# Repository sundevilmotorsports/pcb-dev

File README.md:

# Sun Devil Motorsports Data Acquisition PCB Repository
## About
Various PCB projects for Data Acquisition. Includes:
- SDM-22 Main Board
- SDM-22 Wheel Board
- SDM CAN Board (Texas Instruments SN65HVD230)
- SDM KiCad library (submodule)
- SDM-23 things
- SDM-24 things
## Installation Requirements
- KiCad 6
- `SDM.pretty`, `SDM_kicad`, `teensy.pretty`, `teensy_library` (included here as submodules)
## Installation Instructions
1. Get the project.
```bash
$ git clone --recursive git@github.com:sundevilmotorsports/pcb-dev.git
```
2. Add `SDM.pretty`, `SDM_kicad`, `teensy.pretty`, `teensy_library` as libraries in KiCad.

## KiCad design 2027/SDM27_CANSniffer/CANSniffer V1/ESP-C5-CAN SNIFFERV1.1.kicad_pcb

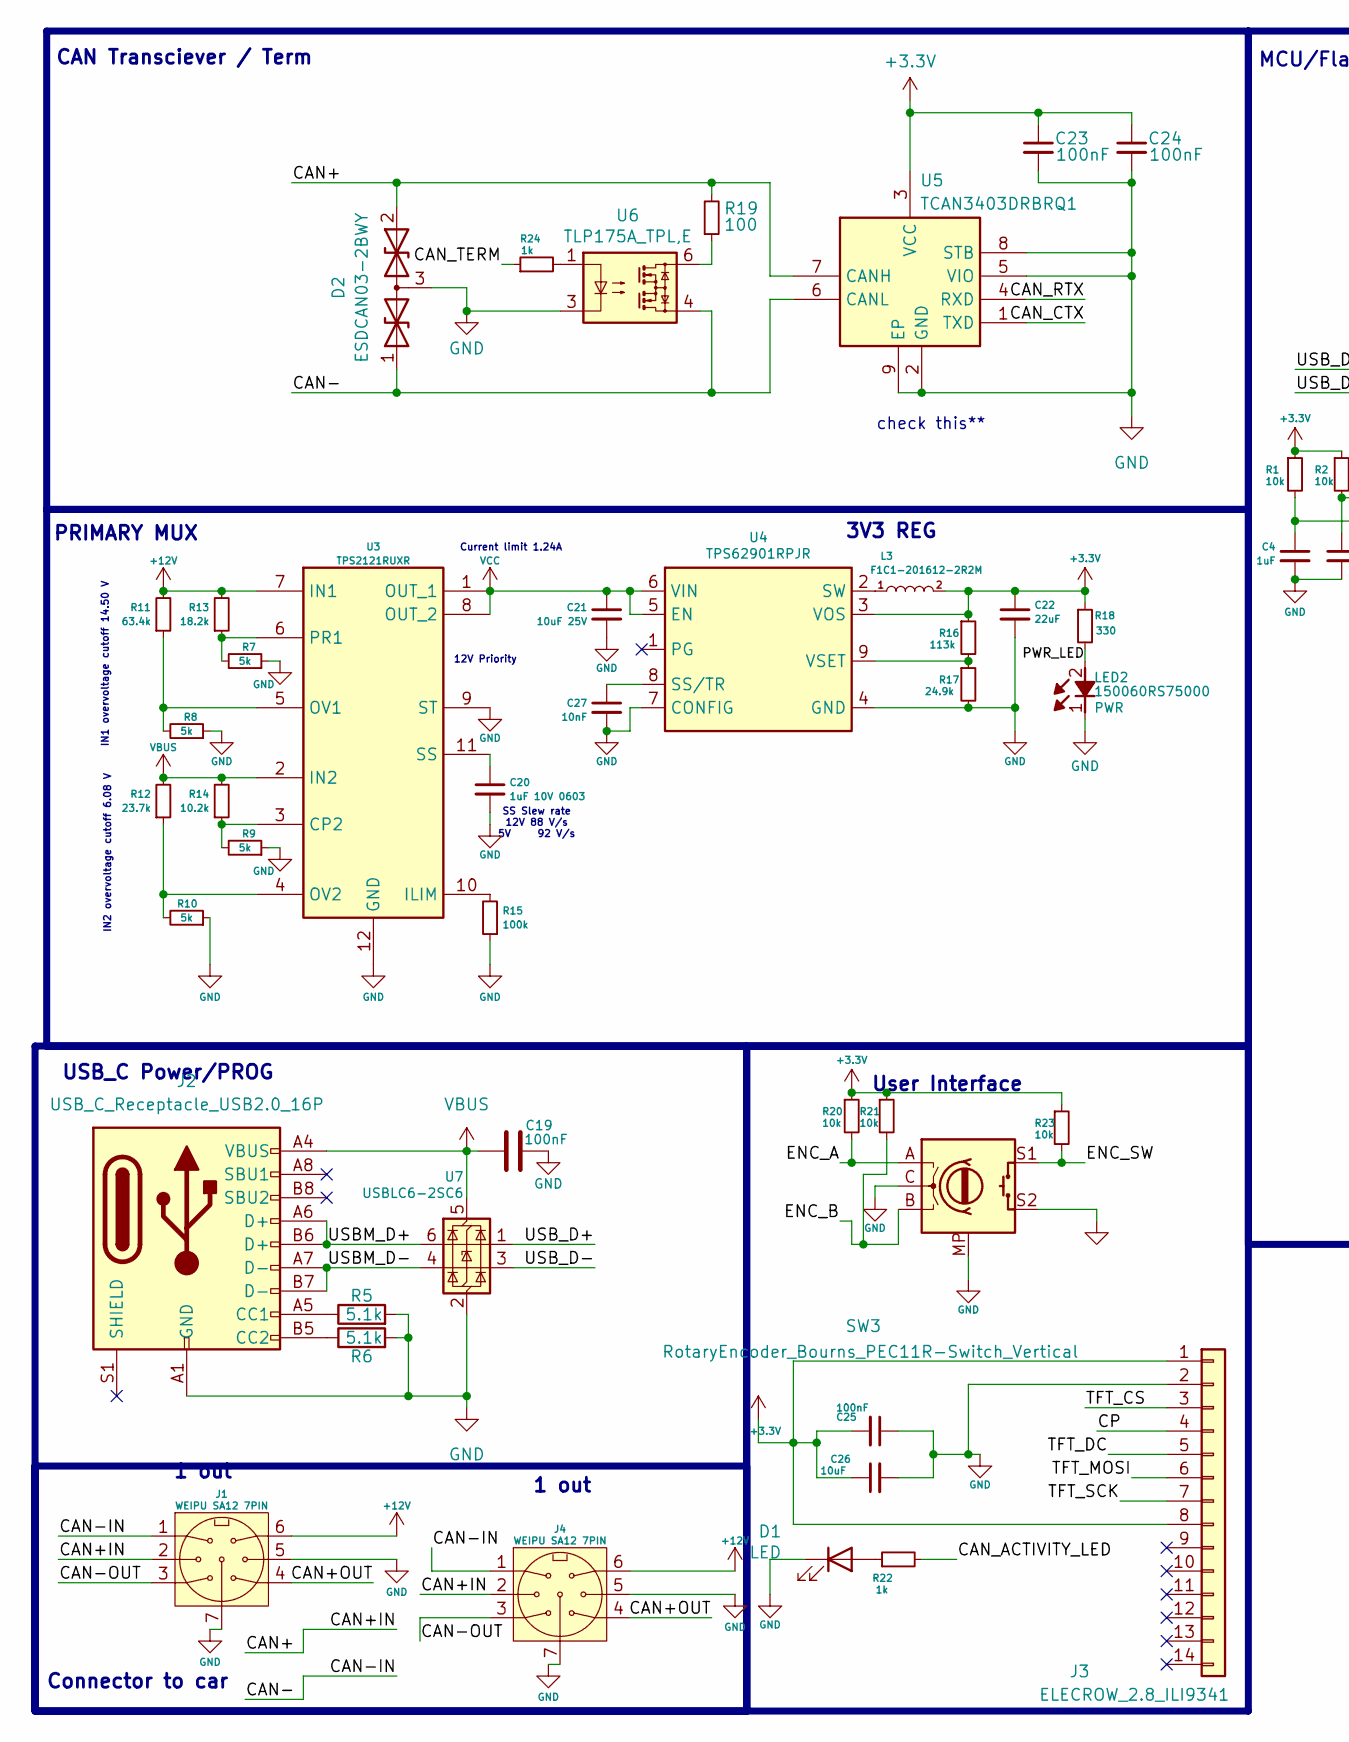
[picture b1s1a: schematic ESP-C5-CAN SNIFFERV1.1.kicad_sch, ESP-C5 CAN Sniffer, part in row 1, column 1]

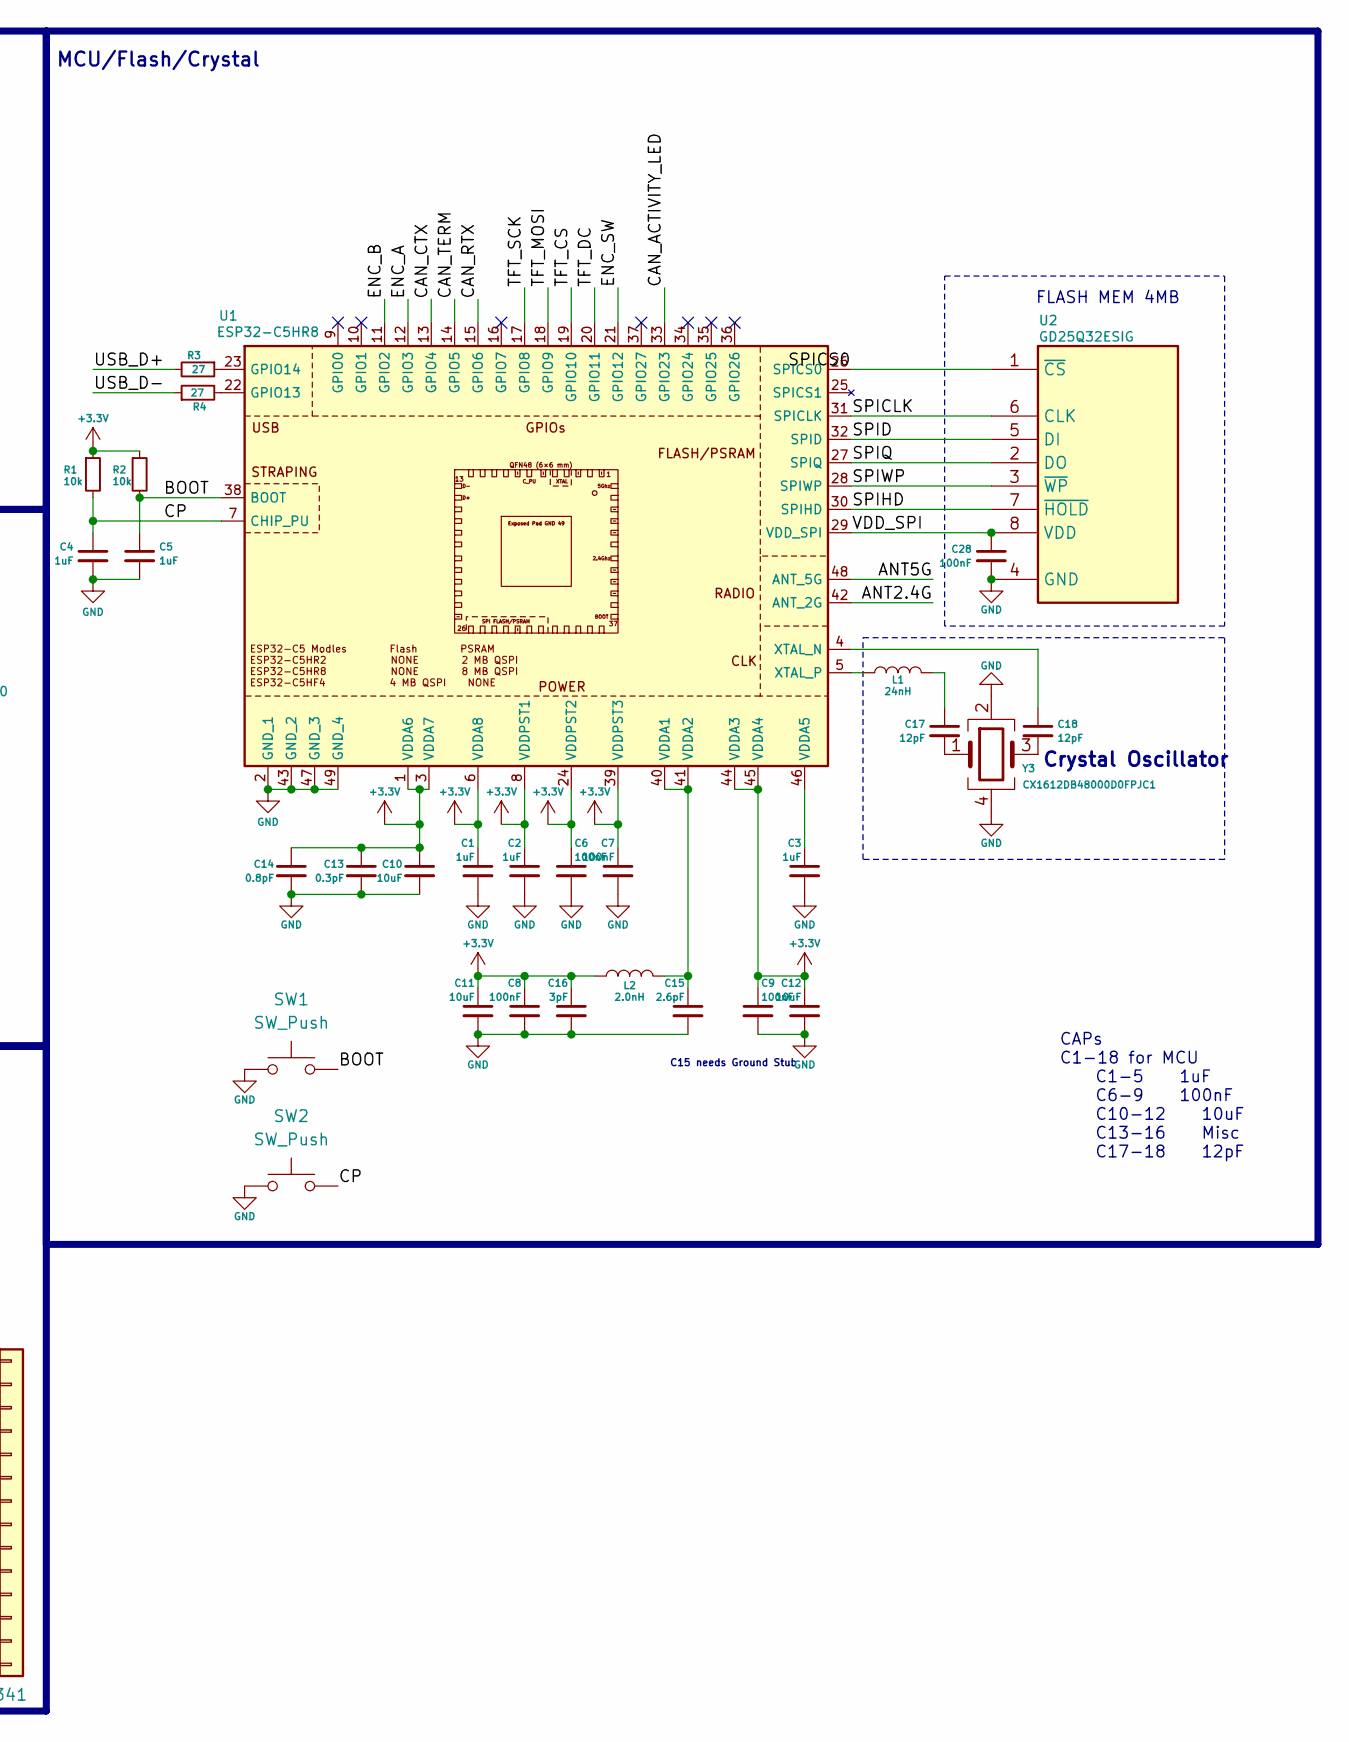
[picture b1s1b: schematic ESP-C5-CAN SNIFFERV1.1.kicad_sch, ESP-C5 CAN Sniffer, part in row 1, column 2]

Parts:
C1, C2, C3, C4, C5: 1uF; C_0603_1608Metric
C6, C7, C8, C9, C19, C23, C24, C25, C28: 100nF; C_0603_1608Metric
C10, C11, C12, C26: 10uF; C_0603_1608Metric
C13: 0.3pF; C_0603_1608Metric
C14: 0.8pF; C_0603_1608Metric
C15: 2.6pF; C_0603_1608Metric
C16: 3pF; C_0603_1608Metric
C17, C18: 12pF; C_0201_0603Metric
C20: 1uF 10V 0603; C_0603_1608Metric
C21: 10uF 25V; C_0603_1608Metric
C22: 22uF; C_0603_1608Metric
C27: 10nF; C_0603_1608Metric
D1: LED; SSFLXH100LID01
D2: ESDCAN03-2BWY; SOT65P210X110-3N; Mouser Part Number 511-ESDCAN03-2BWY
J1, J4: WEIPU SA12 7PIN; PinHeader_1x07_P2.54mm_Vertical
J2: USB_C_Receptacle_USB2.0_16P; USB_C_Receptacle_G-Switch_GT-USB-7010ASVCAN
J3: ELECROW_2.8_ILI9341; PinHeader_1x14_P2.54mm_Vertical
L1: 24nH; L_0402_1005Metric
L2: 2.0nH; L_0402_1005Metric
L3: F1C1-201612-2R2M; F1C12016122R2M; Mouser Part Number 530-F1C1-201612-2R2M
LED2: 150060RS75000; LEDC1608X80N; Mouser Part Number 710-150060RS75000
R1, R2, R20, R21, R23: 10k; R_0402_1005Metric
R3, R4: 27; R_0402_1005Metric
R5, R6: 5.1k; R_0603_1608Metric
R7, R8, R9, R10: 5k; R_0603_1608Metric
R11: 63.4k; R_0603_1608Metric
R12: 23.7k; R_0603_1608Metric
R13: 18.2k; R_0603_1608Metric
R14: 10.2k; R_0603_1608Metric
R15: 100k; R_0603_1608Metric
R16: 113k; R_0603_1608Metric
R17: 24.9k; R_0603_1608Metric
R18: 330; R_0603_1608Metric
R19: 100; R_0603_1608Metric
R22, R24: 1k; R_0402_1005Metric
SW1, SW2: SW_Push; SW_SPST_CK_KXT3
SW3: RotaryEncoder_Bourns_PEC11R-Switch_Vertical; XDCR_PEC11R-4220F-S0024
U1: ESP32-C5HR8; QFN40P600X600X90-49N-D; Manufacturer_Part_Number ESP32-C5HR8
U2: GD25Q32ESIG; SOP-8-1EP_4.57x4.57mm_P1.27mm_EP4.57x4.45mm; Mouser Part Number 363-GD25Q32ESIG
U3: TPS2121RUXR; Mouser Part Number 595-TPS2121RUXR
U4: TPS62901RPJR; Mouser Part Number 595-TPS62901RPJR
U5: TCAN3403DRBRQ1; SON65P300X300X100-9N-D; Manufacturer_Part_Number TCAN3403DRBRQ1; Mouser Part Number 595-TCAN3403DRBRQ1
U6: TLP175A_TPL,E; TLP266J; Mouser Part Number 757-TLP175A(TPLE
U7: USBLC6-2SC6; SOT-23-6
Y3: CX1612DB48000D0FPJC1; Mouser Part Number 581-CX1612DB48D0FPJ

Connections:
+3.3V: C1.1, C2.1, C6.1, C7.1, C8.1, C9.1, C10.1, C11.1, C12.1, C13.1, C14.1, C16.1, C22.1, C23.1, C24.1, C25.2, C26.1, J3.1, J3.8, L2.2, L3.2, R1.1, R2.1, R16.1, R18.1, R20.1, R21.1, R23.1, U1.1 (VDDA6), U1.3 (VDDA7), U1.6 (VDDA8), U1.8 (VDDPST1), U1.24 (VDDPST2), U1.39 (VDDPST3), U1.44 (VDDA3), U1.45 (VDDA4), U4.3 (VOS), U5.3 (VCC); also elsewhere on the board
+12V: J1.6, J4.6, R11.2, R13.2, U3.7 (IN1); also elsewhere on the board
/BOOT: C5.1, R2.2, SW1.2, U1.38 (BOOT); also elsewhere on the board
/CAN+: D2.2, J1.2, J4.2, R19.2, U5.7 (CANH)
/CAN+OUT: J1.4, J4.4
/CAN-: D2.1, J1.1, J4.1, U5.6 (CANL), U6.4
/CAN-OUT: J1.3, J4.3
/CAN_ACTIVITY_LED: R22.2, U1.33 (GPIO23); also elsewhere on the board
/CAN_CTX: U1.13 (GPIO4), U5.1 (TXD); also elsewhere on the board
/CAN_RTX: U1.15 (GPIO6), U5.4 (RXD); also elsewhere on the board
/CAN_TERM: R24.1, U1.14 (GPIO5); also elsewhere on the board
/CP: C4.1, J3.4, R1.2, SW2.2, U1.7 (CHIP_PU); also elsewhere on the board
/ENC_A: R20.2, SW3.A, U1.12 (GPIO3); also elsewhere on the board
/ENC_B: R21.2, SW3.B, U1.11 (GPIO2); also elsewhere on the board
/ENC_SW: R23.2, SW3.S1, U1.21 (GPIO12); also elsewhere on the board
/PWR_LED: LED2.2 (A), R18.2
/SPICLK: U1.31 (SPICLK), U2.6 (CLK); also elsewhere on the board
/SPICS0: U1.26 (SPICS0), U2.1 (~CS); also elsewhere on the board
/SPID: U1.32 (SPID), U2.5 (DI); also elsewhere on the board
/SPIHD: U1.30 (SPIHD), U2.7 (~HOLD); also elsewhere on the board
/SPIQ: U1.27 (SPIQ), U2.2 (DO); also elsewhere on the board
/SPIWP: U1.28 (SPIWP), U2.3 (~WP); also elsewhere on the board
/TFT_CS: J3.3, U1.19 (GPIO10); also elsewhere on the board
/TFT_DC: J3.5, U1.20 (GPIO11); also elsewhere on the board
/TFT_MOSI: J3.6, U1.18 (GPIO9); also elsewhere on the board
/TFT_SCK: J3.7, U1.17 (GPIO8); also elsewhere on the board
/USBM_D+: J2.A6 (D+), J2.B6 (D+), U7.6 (I/O1)
/USBM_D-: J2.A7 (D-), J2.B7 (D-), U7.4 (I/O2)
/USB_D+: R3.2, U7.1 (I/O1)
/USB_D-: R4.1, U7.3 (I/O2)
/VDD_SPI: C28.1, U1.29 (VDD_SPI), U2.8 (VDD); also elsewhere on the board
GND: C1.2, C2.2, C3.2, C4.2, C5.2, C6.2, C7.2, C8.2, C9.2, C10.2, C11.2, C12.2, C13.2, C14.2, C15.2, C16.2, C19.1, C20.2, C21.2, C22.2, C23.2, C24.2, C25.1, C26.2, C27.2, C28.2, D1.1 (K), D2.3, J1.5, J1.7, J2.A1 (GND), J2.A12 (GND), J2.B1 (GND), J2.B12 (GND), J2.S1 (SHIELD), J3.2, J4.5, J4.7, LED2.1 (K), R5.2, R6.2, R7.1, R8.1, R9.1, R10.1, R15.1, R17.2, SW1.1, SW2.1, SW3.C, SW3.MP, SW3.S2, U1.2 (GND_1), U1.43 (GND_2), U1.47 (GND_3), U1.49 (GND_4), U2.4 (GND), U3.9 (ST), U3.12 (GND), U4.4 (GND), U4.7 (CONFIG), U5.2 (GND), U5.5 (VIO), U5.8 (STB), U5.9 (EP), U6.3, U7.2 (GND), Y3.2, Y3.4; also elsewhere on the board
unnamed: C17.1, L1.2
unnamed: C17.2, Y3.1
unnamed: C18.2, Y3.3
unnamed: D1.2 (A), R22.1
unnamed: J2.A5 (CC1), R5.1
unnamed: J2.B5 (CC2), R6.1
unnamed: R19.1, U6.6
unnamed: R24.2, U6.1
unnamed: R9.2, R14.1, U3.3 (CP2)
unnamed: R15.2, U3.10 (ILIM)
unnamed: R8.2, R11.1, U3.5 (OV1)
unnamed: R10.2, R12.1, U3.4 (OV2)
unnamed: R7.2, R13.1, U3.6 (PR1)
unnamed: C20.1, U3.11 (SS)
unnamed: C27.1, U4.8 (SS/TR)
unnamed: L3.1, U4.2 (SW)
unnamed: R16.2, R17.1, U4.9 (VSET)
unnamed 53: R4.2, U1.22 (GPIO13); also elsewhere on the board
unnamed 54: R3.1, U1.23 (GPIO14); also elsewhere on the board
unnamed 55: C15.1, L2.1, U1.40 (VDDA1), U1.41 (VDDA2); also elsewhere on the board
unnamed 56: C3.1, U1.46 (VDDA5); also elsewhere on the board
unnamed 57: C18.1, U1.4 (XTAL_N); also elsewhere on the board
unnamed 58: L1.1, U1.5 (XTAL_P); also elsewhere on the board
VBUS: C19.2, J2.A4 (VBUS), J2.A9 (VBUS), J2.B4 (VBUS), J2.B9 (VBUS), R12.2, R14.2, U3.2 (IN2), U7.5 (VBUS)
VCC: C21.1, U3.1 (OUT_1), U3.8 (OUT_2), U4.5 (EN), U4.6 (VIN)

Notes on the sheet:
3V3 REG
Connector to car
Current limit 1.24A
FLASH MEM 4MB
CAPs C1-18 for MCU C1-5 1uF C6-9 100nF C10-12 10uF C13-16 Misc C17-18 12pF
1 out
SS Slew rate 12V 88 V/s 5V 92 V/s
PRIMARY MUX
MCU/Flash/Crystal
User Interface
12V Priority
IN1 overvoltage cutoff 14.50 V
CAN Transciever / Term
IN2 overvoltage cutoff 6.08 V
C15 needs Ground Stub
Crystal Oscillator
USB_C Power/PROG
check this**

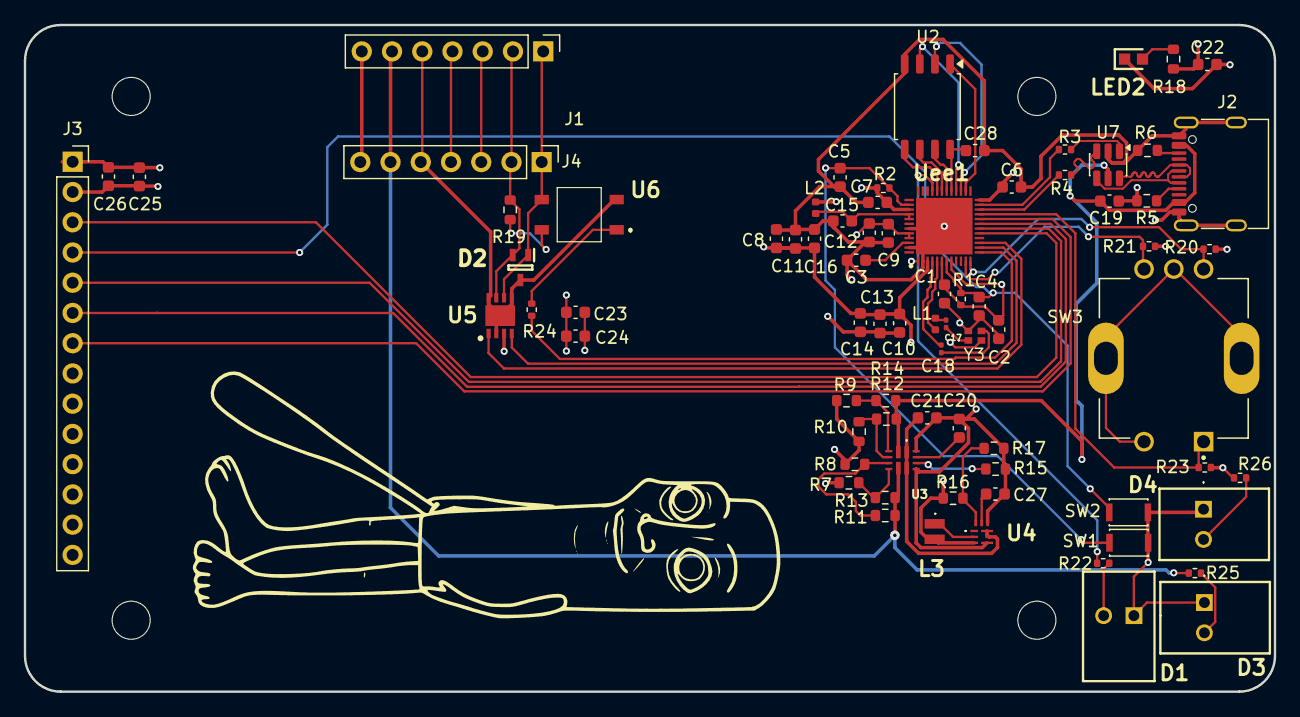
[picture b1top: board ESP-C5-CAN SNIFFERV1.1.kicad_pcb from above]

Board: 4 copper layers, 105.0 x 56.0 mm, 77 parts (0 on the bottom side), 59 nets.

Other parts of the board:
D3, D4: LED; SSFLXH100LID01
R25: 4.7k; R_0402_1005Metric
R26: 680; R_0402_1005Metric
Uee1: ESP32-C5HR8; QFN40P600X600X90-49N-D

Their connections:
+3.3V: R26.2, Uee1.1 (VDDA6), Uee1.3 (VDDA7), Uee1.6 (VDDA8), Uee1.8 (VDDPST1), Uee1.24 (VDDPST2), Uee1.39 (VDDPST3), Uee1.44 (VDDA3), Uee1.45 (VDDA4); also elsewhere on the board
+12V: R25.2; also elsewhere on the board
/BOOT: Uee1.38 (BOOT); also elsewhere on the board
/CAN_ACTIVITY_LED: Uee1.33 (GPIO23); also elsewhere on the board
/CAN_CTX: Uee1.15 (GPIO6); also elsewhere on the board
/CAN_RTX: Uee1.14 (GPIO5); also elsewhere on the board
/CAN_TERM: Uee1.13 (GPIO4); also elsewhere on the board
/CP: Uee1.7 (CHIP_PU); also elsewhere on the board
/ENC_A: Uee1.12 (GPIO3); also elsewhere on the board
/ENC_B: Uee1.11 (GPIO2); also elsewhere on the board
/ENC_SW: Uee1.21 (GPIO12); also elsewhere on the board
/SPICLK: Uee1.31 (SPICLK); also elsewhere on the board
/SPICS0: Uee1.26 (SPICS0); also elsewhere on the board
/SPID: Uee1.32 (SPID); also elsewhere on the board
/SPIHD: Uee1.30 (SPIHD); also elsewhere on the board
/SPIQ: Uee1.27 (SPIQ); also elsewhere on the board
/SPIWP: Uee1.28 (SPIWP); also elsewhere on the board
/TFT_CS: Uee1.17 (GPIO8); also elsewhere on the board
/TFT_DC: Uee1.18 (GPIO9); also elsewhere on the board
/TFT_MOSI: Uee1.19 (GPIO10); also elsewhere on the board
/TFT_SCK: Uee1.20 (GPIO11); also elsewhere on the board
/VDD_SPI: Uee1.29 (VDD_SPI); also elsewhere on the board
GND: D3.1 (K), D4.1 (K), Uee1.2 (GND_1), Uee1.43 (GND_2), Uee1.47 (GND_3), Uee1.49 (GND_4); also elsewhere on the board
unnamed: D3.2 (A), R25.1
unnamed: D4.2 (A), R26.1
unnamed 53: Uee1.22 (GPIO13); also elsewhere on the board
unnamed 54: Uee1.23 (GPIO14); also elsewhere on the board
unnamed 55: Uee1.40 (VDDA1), Uee1.41 (VDDA2); also elsewhere on the board
unnamed 56: Uee1.46 (VDDA5); also elsewhere on the board
unnamed 57: Uee1.4 (XTAL_N); also elsewhere on the board
unnamed 58: Uee1.5 (XTAL_P); also elsewhere on the board

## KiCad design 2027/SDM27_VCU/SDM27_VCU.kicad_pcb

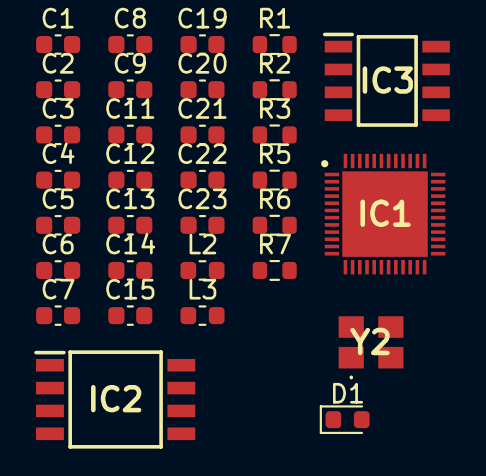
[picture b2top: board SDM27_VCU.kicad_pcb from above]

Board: 2 copper layers, 32 parts (0 on the bottom side), 20 nets, no tracks yet.

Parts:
C1: 0.8pF; C_0603_1608Metric
C2, C3: 12pF; C_0603_1608Metric
C4: 0.3pF; C_0603_1608Metric
C5, C19, C23: 10uF; C_0603_1608Metric
C6, C8, C14: 1uF; C_0603_1608Metric
C7, C11, C13, C20, C22: 0.1uF; C_0603_1608Metric
C9: 2.6pF; C_0603_1608Metric
C12: 10nF; C_0603_1608Metric
C15: 1 uF; C_0603_1608Metric
C21: 3.0pF; C_0603_1608Metric
D1: D_TVS (ESD); D_0603_1608Metric
IC1: ESP32-C5HR8; QFN40P600X600X90-49N-D
IC2: SST26VF064B-104I_SM; SOIC127P794X203-8N
IC3: IS66WVR8M8FBLL-104NLI; SOIC127P600X175-8N
L2: 24nH; L_0603_1608Metric
L3: 2nH; L_0603_1608Metric
R1: 499; R_0603_1608Metric
R2, R3, R5, R6, R7: 0; R_0603_1608Metric
Y2: CX3225FB48000F0FZZH1

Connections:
/SPICLK: IC2.6 (CLK), IC3.6 (CLK), R6.2
/SPICS0: IC1.26 (SPICS0), IC2.1 (~CS)
/SPICS1_IO15: IC1.25 (SPICS1), IC3.1 (~CS)
/SPID: IC2.5 (DI), IC3.5 (DI), R7.2
/SPIHD: IC2.7 (~HOLD), IC3.7 (~HOLD), R5.2
/SPIQ: IC2.2 (DO), IC3.2 (DO), R2.2
/SPIWP: IC2.3 (~WP), IC3.3 (~WP), R3.2
/VDD33: C1.1, C4.1, C5.1, C6.1, C7.1, C8.1, C11.1, C12.1, C13.1, C14.1, C19.1, C21.1, C22.1, C23.1, D1.1 (A1), IC1.1 (VDDA6), IC1.3 (VDDA7), IC1.6 (VDDA8), IC1.8 (VDDPST1), IC1.24 (VDDPST2), IC1.39 (VDDPST3), IC1.44 (VDDA3), IC1.45 (VDDA4), IC1.46 (VDDA5), L3.2
/VDD_SPI: C15.1, C20.1, IC1.29 (VDD_SPI), IC2.8 (VDD), IC3.8 (VDD)
/XTAL_N: C2.2, IC1.4 (XTAL_N), Y2.3 (X_OUT)
/XTAL_P: C3.2, L2.1, Y2.1 (X_IN)
GND: C1.2, C2.1, C3.1, C4.2, C5.2, C6.2, C7.2, C8.2, C9.2, C11.2, C12.2, C13.2, C14.2, C15.2, C19.2, C20.2, C21.2, C22.2, C23.2, D1.2 (A2), IC1.2 (GND_1), IC1.43 (GND_2), IC1.47 (GND_3), IC1.49 (GND_4), IC2.4 (GND), IC3.4 (GND), Y2.2 (GND_1), Y2.4 (GND_2)
unnamed: IC1.31 (SPICLK), R6.1
unnamed: IC1.32 (SPID), R7.1
unnamed: IC1.30 (SPIHD), R5.1
unnamed: IC1.27 (SPIQ), R2.1
unnamed: IC1.28 (SPIWP), R3.1
unnamed: IC1.20 (U0TXD), R1.1
unnamed: C9.1, IC1.40 (VDDA1), IC1.41 (VDDA2), L3.1
unnamed: IC1.5 (XTAL_P), L2.2

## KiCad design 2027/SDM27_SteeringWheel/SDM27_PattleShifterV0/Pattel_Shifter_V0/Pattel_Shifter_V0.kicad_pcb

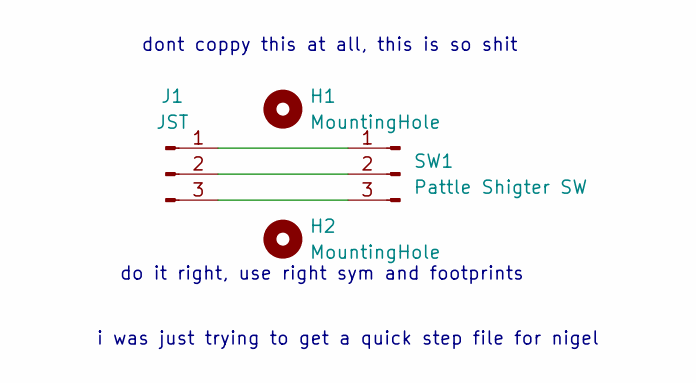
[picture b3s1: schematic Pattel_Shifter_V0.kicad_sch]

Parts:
H1, H2: MountingHole; MountingHole_2.2mm_M2
J1: JST; JST_EH_S3B-EH_1x03_P2.50mm_Horizontal
SW1: Pattle Shigter SW; SW_Slide_SPDT_Straight_CK_OS102011MS2Q

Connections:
unnamed: J1.1, SW1.1
unnamed: J1.2, SW1.2
unnamed: J1.3, SW1.3

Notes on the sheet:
dont coppy this at all, this is so shit
i was just trying to get a quick step file for nigel
do it right, use right sym and footprints

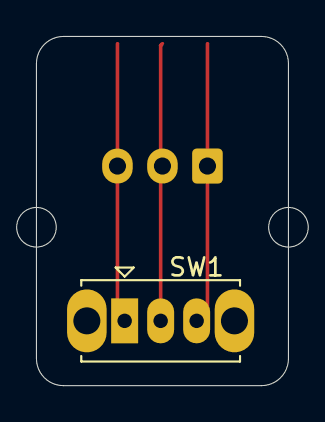
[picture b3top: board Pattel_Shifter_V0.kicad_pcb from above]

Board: 2 copper layers, 14.0 x 19.4 mm, 4 parts (1 on the bottom side), 3 nets.

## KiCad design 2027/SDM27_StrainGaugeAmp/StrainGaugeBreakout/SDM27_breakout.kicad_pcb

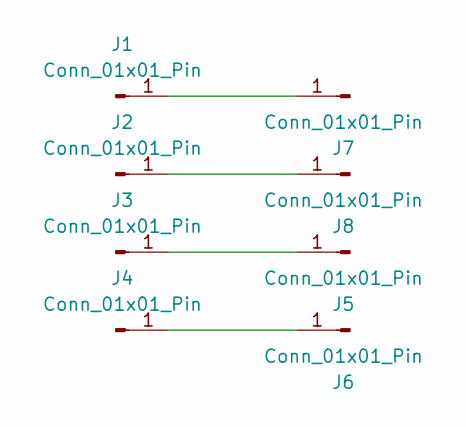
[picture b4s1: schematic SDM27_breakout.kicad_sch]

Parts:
J1, J2, J3, J4: Conn_01x01_Pin; SolderWirePad_1x01_SMD_1x2mm
J5, J6, J7, J8: Conn_01x01_Pin; SolderWirePad_1x01_SMD_2x4mm

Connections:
unnamed: J1.1 (Pin_1_1), J7.1 (Pin_1_1)
unnamed: J2.1 (Pin_1_1), J8.1 (Pin_1_1)
unnamed: J3.1 (Pin_1_1), J5.1 (Pin_1_1)
unnamed: J4.1 (Pin_1_1), J6.1 (Pin_1_1)

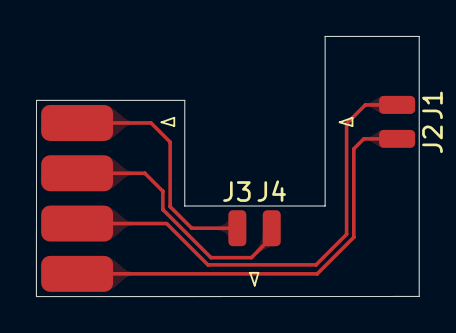
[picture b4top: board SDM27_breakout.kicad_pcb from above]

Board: 2 copper layers, 21.3 x 14.5 mm, 8 parts (0 on the bottom side), 4 nets.

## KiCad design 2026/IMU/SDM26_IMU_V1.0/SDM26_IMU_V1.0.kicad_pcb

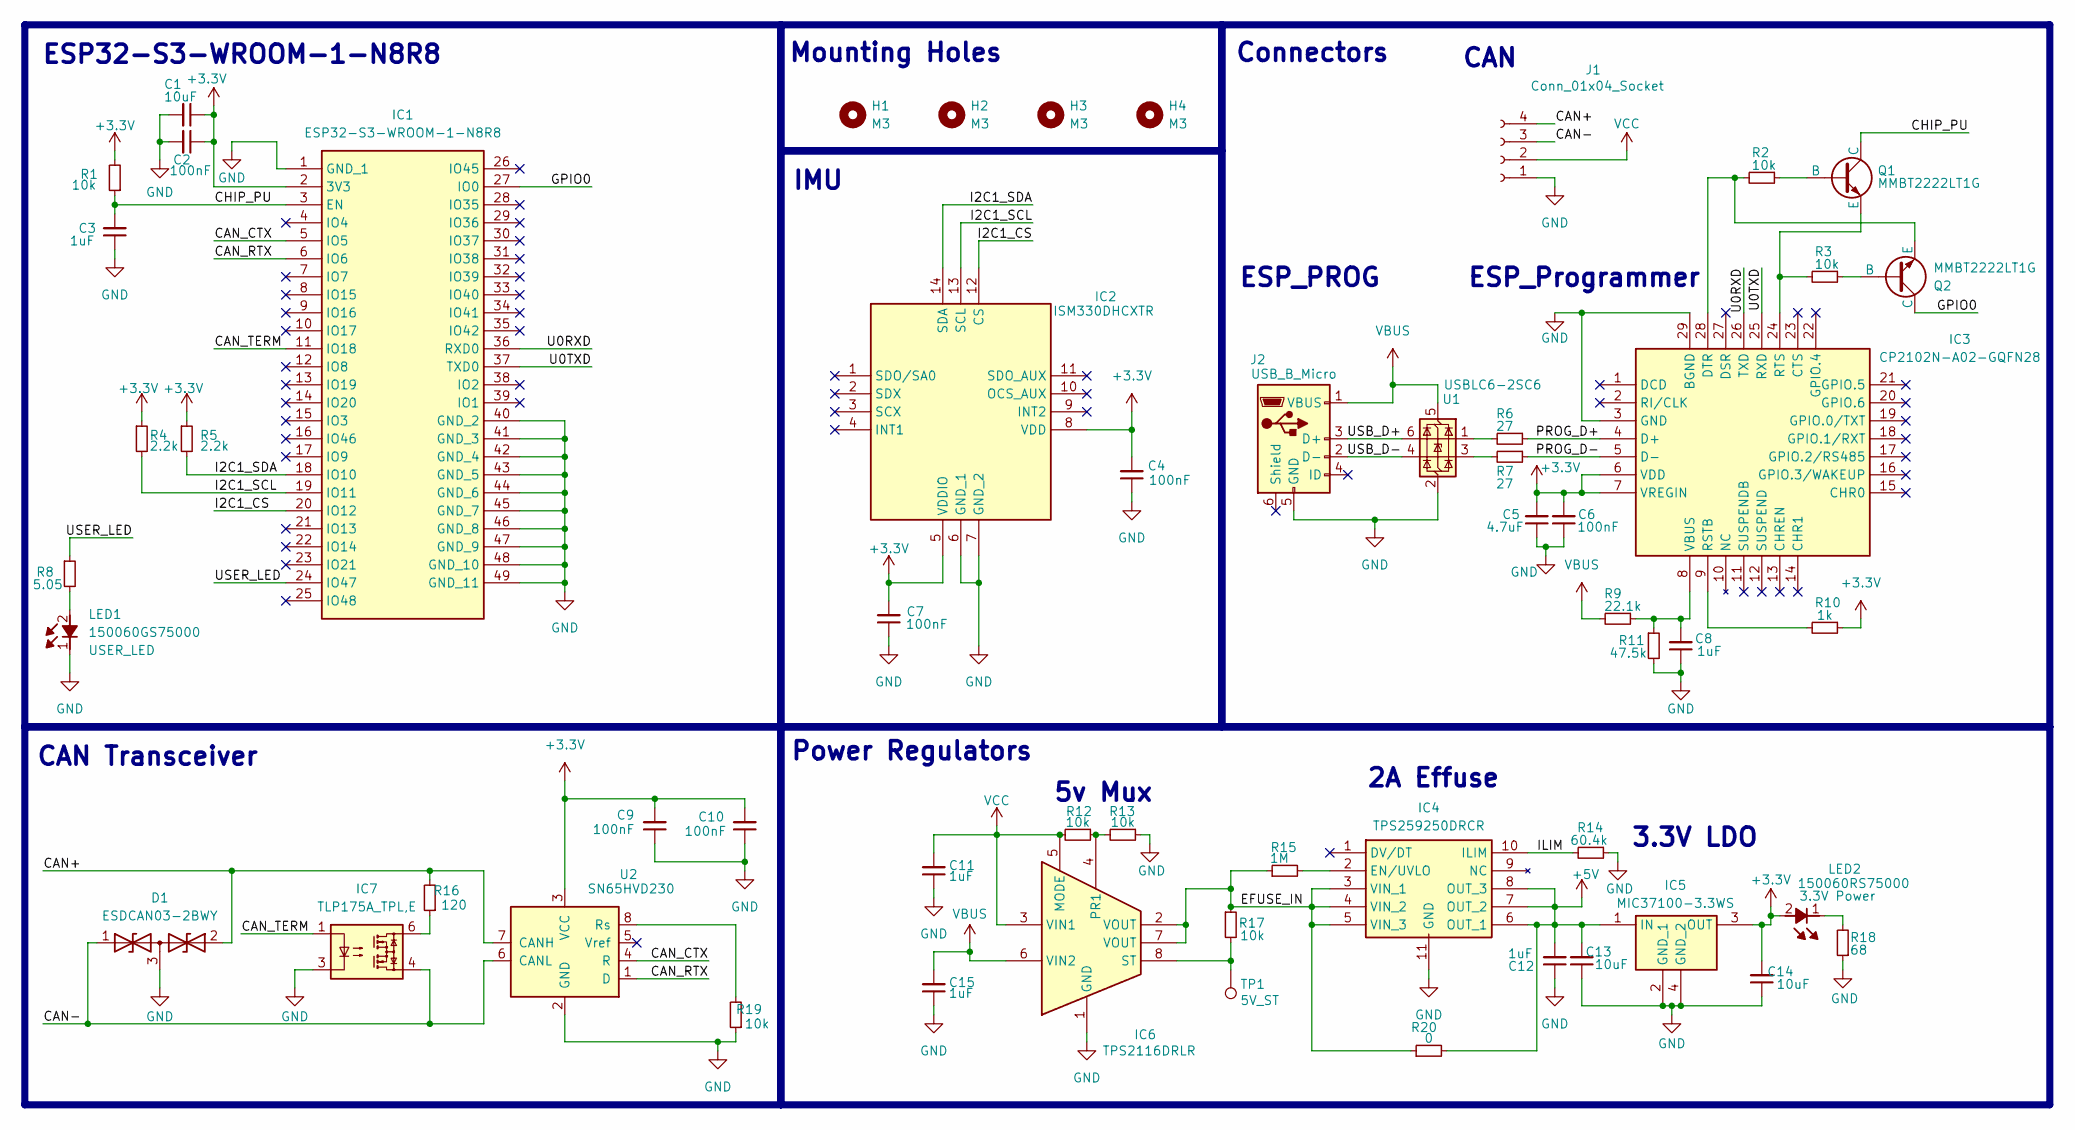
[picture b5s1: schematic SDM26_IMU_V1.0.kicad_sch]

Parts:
C1, C13, C14: 10uF; C_0603_1608Metric
C2, C4, C6, C7, C9, C10: 100nF; C_0603_1608Metric
C3, C8, C11, C12, C15: 1uF; C_0603_1608Metric
C5: 4.7uF; C_0603_1608Metric
D1: ESDCAN03-2BWY; SOT65P210X110-3N; Mouser Part Number 511-ESDCAN03-2BWY
H1, H2, H3, H4: M3; MountingHole_3.2mm_M3
IC1: ESP32-S3-WROOM-1-N8R8; ESP32S3WROOM1N8R8; Mouser Part Number 356-EP32S3WROOM1N8R8
IC2: ISM330DHCXTR; LSM6DS3USTR; Mouser Part Number 511-ISM330DHCXTR
IC3: CP2102N-A02-GQFN28; QFN50P500X500X80-29N-D; Mouser Part Number 634-CP2102NA02GQFN28
IC4: TPS259250DRCR; SON50P300X300X100-11L-D; Mouser Part Number 595-TPS259250DRCR
IC5: MIC37100-3.3WS; SOT230P700X180-4N; Mouser Part Number 998-MIC37100-3.3WS
IC6: TPS2116DRLR; SOTFL50P160X60-8L; Mouser Part Number 595-TPS2116DRLR
IC7: TLP175A_TPL,E; TLP266J; Mouser Part Number 757-TLP175A(TPLE
J1: Conn_01x04_Socket; JST_XH_S4B-XH-A_1x04_P2.50mm_Horizontal
J2: USB_B_Micro; USB_Micro-B_Molex-105017-0001
LED1: 150060GS75000; LEDC1608X80N; Mouser Part Number 710-150060VS75000
LED2: 150060RS75000; LEDC1608X80N; Mouser Part Number 710-150060RS75000
Q1, Q2: MMBT2222LT1G; SOT96P237X111-3N
R1, R2, R3, R12, R13, R17, R19: 10k; R_0603_1608Metric
R4, R5: 2.2k; R_0603_1608Metric
R6, R7: 27; R_0603_1608Metric
R8: 5.05; R_0603_1608Metric
R9: 22.1k; R_0603_1608Metric
R10: 1k; R_0603_1608Metric
R11: 47.5k; R_0603_1608Metric
R14: 60.4k; R_0603_1608Metric
R15: 1M; R_0603_1608Metric
R16: 120; R_0603_1608Metric
R18: 68; R_0603_1608Metric
R20: 0; R_0603_1608Metric
TP1: 5V_ST; TestPoint_Pad_1.5x1.5mm
U1: USBLC6-2SC6; SOT-23-6
U2: SN65HVD230; SOIC-8_3.9x4.9mm_P1.27mm

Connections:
+3.3V: C1.1, C2.1, C4.2, C5.2, C6.2, C7.2, C9.2, C10.2, C14.2, IC1.2 (3V3), IC2.5 (VDDIO), IC2.8 (VDD), IC3.6 (VDD), IC3.7 (VREGIN), IC5.3 (OUT), LED2.2 (A), R1.2, R4.1, R5.1, R10.1, U2.3 (VCC)
+5V: C12.2, C13.2, IC4.6 (OUT_1), IC4.7 (OUT_2), IC4.8 (OUT_3), IC5.1 (IN), R20.2
/CAN+: D1.2, J1.4, R16.2, U2.7 (CANH)
/CAN-: D1.1, IC7.4, J1.3, U2.6 (CANL)
/CAN_CTX: IC1.5 (IO5), U2.4 (R)
/CAN_RTX: IC1.6 (IO6), U2.1 (D)
/CAN_TERM: IC1.11 (IO18), IC7.1
/CHIP_PU: C3.2, IC1.3 (EN), Q1.3 (C), R1.1
/EFUSE_IN: IC4.3 (VIN_1), IC4.4 (VIN_2), IC4.5 (VIN_3), IC6.2 (VOUT), IC6.7 (VOUT), R15.1, R17.1, R20.1
/GPIO0: IC1.27 (IO0), Q2.3 (C)
/I2C1_CS: IC1.20 (IO12), IC2.12 (CS)
/I2C1_SCL: IC1.19 (IO11), IC2.13 (SCL), R4.2
/I2C1_SDA: IC1.18 (IO10), IC2.14 (SDA), R5.2
/ILIM: IC4.10 (ILIM), R14.2
/PROG_D+: IC3.4 (D+), R6.1
/PROG_D-: IC3.5 (D-), R7.1
/U0RXD: IC1.36 (RXD0), IC3.26 (TXD)
/U0TXD: IC1.37 (TXD0), IC3.25 (RXD)
/USB_D+: J2.3 (D+), U1.6 (I/O1)
/USB_D-: J2.2 (D-), U1.4 (I/O2)
/USER_LED: IC1.24 (IO47), R8.1
GND: C1.2, C2.2, C3.1, C4.1, C5.1, C6.1, C7.1, C8.1, C9.1, C10.1, C11.1, C12.1, C13.1, C14.1, C15.1, D1.3, IC1.1 (GND_1), IC1.40 (GND_2), IC1.41 (GND_3), IC1.42 (GND_4), IC1.43 (GND_5), IC1.44 (GND_6), IC1.45 (GND_7), IC1.46 (GND_8), IC1.47 (GND_9), IC1.48 (GND_10), IC1.49 (GND_11), IC2.6 (GND_1), IC2.7 (GND_2), IC3.3 (GND), IC3.29 (BGND), IC4.11 (GND), IC5.2 (GND_1), IC5.4 (GND_2), IC6.1 (GND), IC7.3, J1.1, J2.5 (GND), LED1.1 (K), R11.2, R13.1, R14.1, R18.1, R19.1, U1.2 (GND), U2.2 (GND)
unnamed: IC3.28 (DTR), Q2.2 (E), R2.2
unnamed: IC3.9 (RSTB), R10.2
unnamed: IC3.24 (RTS), Q1.2 (E), R3.2
unnamed: C8.2, IC3.8 (VBUS), R9.1, R11.1
unnamed: IC4.2 (EN/UVLO), R15.2
unnamed: IC6.4 (PR1), R12.1, R13.2
unnamed: IC6.8 (ST), R17.2, TP1.1
unnamed: IC7.6, R16.1
unnamed: LED1.2 (A), R8.2
unnamed: LED2.1 (K), R18.2
unnamed: Q1.1 (B), R2.1
unnamed: Q2.1 (B), R3.1
unnamed: R6.2, U1.1 (I/O1)
unnamed: R7.2, U1.3 (I/O2)
unnamed: R19.2, U2.8 (Rs)
VBUS: C15.2, IC6.6 (VIN2), J2.1 (VBUS), R9.2, U1.5 (VBUS)
VCC: C11.2, IC6.3 (VIN1), IC6.5 (MODE), J1.2, R12.2

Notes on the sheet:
3.3V LDO
Mounting Holes
ESP_Programmer
Connectors
IMU
5v Mux
ESP32-S3-WROOM-1-N8R8
Power Regulators
CAN
ESP_PROG
2A Effuse
CAN Transceiver

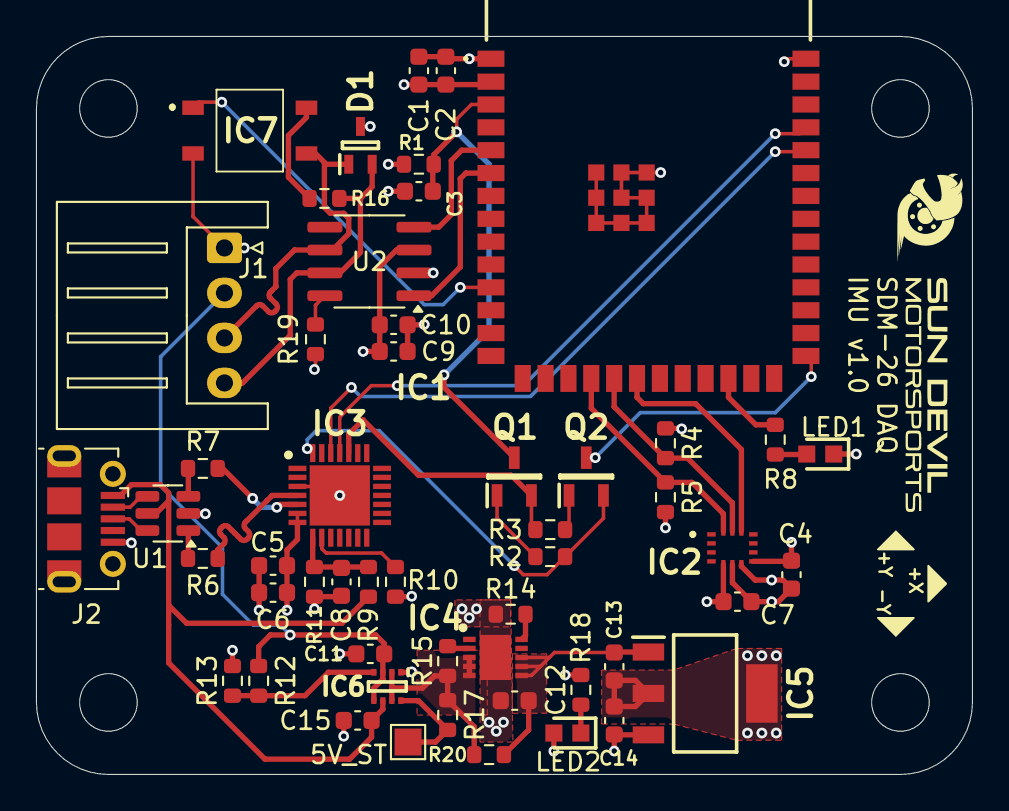
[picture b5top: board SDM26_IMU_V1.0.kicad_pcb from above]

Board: 4 copper layers, 52.0 x 41.0 mm, 56 parts (0 on the bottom side), 39 nets.

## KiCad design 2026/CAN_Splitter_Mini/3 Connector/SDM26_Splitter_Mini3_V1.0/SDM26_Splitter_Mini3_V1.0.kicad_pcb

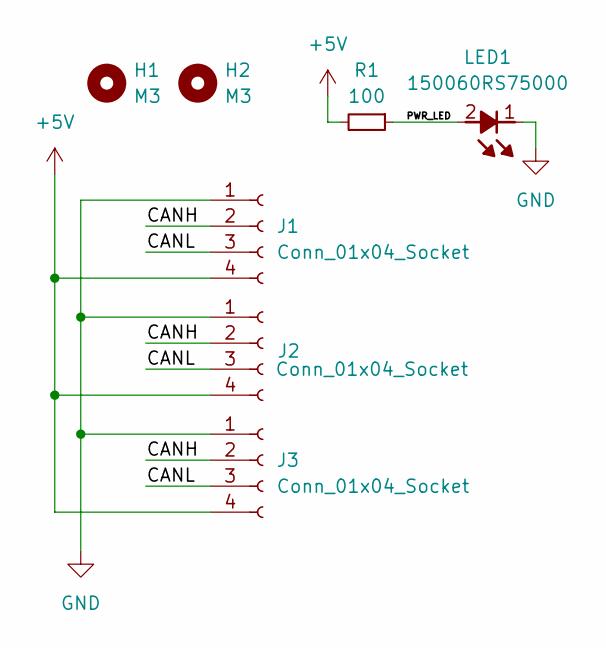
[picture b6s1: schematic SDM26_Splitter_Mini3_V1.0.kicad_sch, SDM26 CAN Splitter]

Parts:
H1, H2: M3; MountingHole_3.2mm_M3
J1, J2, J3: Conn_01x04_Socket; JST_EH_S4B-EH_1x04_P2.50mm_Horizontal
LED1: 150060RS75000; LEDC1608X80N; Mouser Part Number 710-150060RS75000
R1: 100; C_0603_1608Metric

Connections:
+5V: J1.4, J2.4, J3.4, R1.2
/CANH: J1.2, J2.2, J3.2
/CANL: J1.3, J2.3, J3.3
/PWR_LED: LED1.2 (A), R1.1
GND: J1.1, J2.1, J3.1, LED1.1 (K)

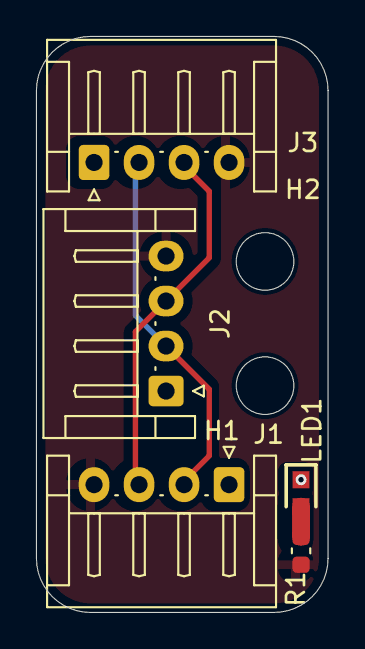
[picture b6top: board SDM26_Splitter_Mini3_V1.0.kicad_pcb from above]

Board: 2 copper layers, 16.2 x 32.0 mm, 7 parts (0 on the bottom side), 5 nets.
